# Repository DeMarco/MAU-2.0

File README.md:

View this project on [CADLAB.io](https://cadlab.io/project/1286). 

# MAU-2.0
The expanded version of MAU

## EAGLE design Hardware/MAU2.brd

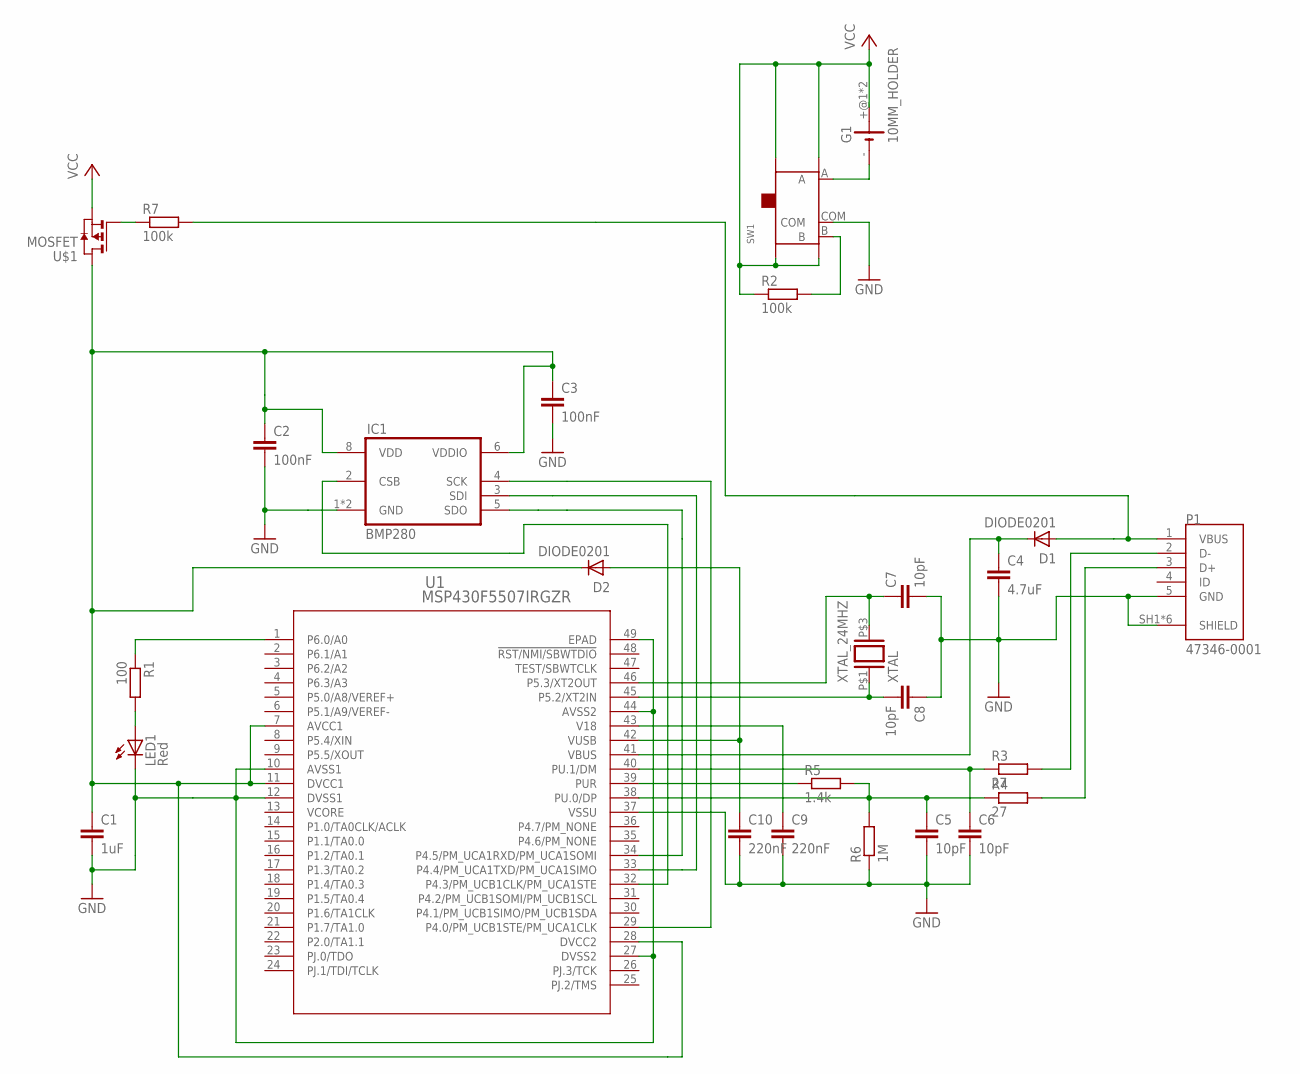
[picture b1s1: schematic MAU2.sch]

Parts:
C1: 1uF; C0201
C2, C3: 100nF; C0201
C4: 4.7uF; C0201
C5, C6, C7, C8: 10pF; C0201
C9, C10: 220nF; C0201
D1, D2: DIODE0201; 0201
G1: 10MM_HOLDER
IC1: BMP280
LED1: Red; CHIPLED_0603
P1: 47346-0001; MOLEX_47346-0001
R1: 100; R0201
R2, R7: 100k; R0201
R3, R4: 27; R0201
R5: 1.4k; R0201
R6: 1M; R0201
SW1: SMD-TOGGLE-SWITCH-ON-ON(3+4P-6.7X2.7MM)SLIDE_LATE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; SW7-SMD-6.7X2.6X1.4MM-90D
U1: MSP430F5507IRGZR; RGZ48_5P15X5P15
U$1: MOSFET; VLM0806
XTAL_24MHZ: XTAL; XTAL_SMD_1612

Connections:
GND: C1.2, C2.2, C3.2, C4.2, C5.2, C6.2, C7.2, C8.1, C9.2, C10.2, IC1.1 (GND), IC1.7 (GND), LED1.C, P1.5 (GND), P1.SH1 (SHIELD), P1.SH2 (SHIELD), P1.SH3 (SHIELD), P1.SH4 (SHIELD), P1.SH5 (SHIELD), P1.SH6 (SHIELD), R6.1, SW1.COM, U1.10 (AVSS1), U1.12 (DVSS1), U1.27 (DVSS2), U1.37 (VSSU), U1.44 (AVSS2), U1.49 (EPAD)
unnamed: G1.-, SW1.A
unnamed: C4.1, D1.1 (C), U1.41 (VBUS)
unnamed: LED1.A, R1.2
unnamed: C6.1, R3.1, U1.40 (PU.1/DM)
unnamed: R2.2, SW1.B
unnamed: C5.1, R4.1, R5.2, R6.2, U1.38 (PU.0/DP)
unnamed: P1.2 (D-), R3.2
unnamed: P1.3 (D+), R4.2
unnamed: R5.1, U1.39 (PUR)
unnamed: C8.2, U1.45 (P5.2/XT2IN), XTAL_24MHZ.P$1 (1)
unnamed: C7.1, U1.46 (P5.3/XT2OUT), XTAL_24MHZ.P$3 (2)
unnamed: C9.1, U1.43 (V18)
unnamed: C10.1, D2.2 (A), U1.42 (VUSB)
unnamed: R7.1, U$1.P$1 (G)
unnamed: IC1.5 (SDO), U1.34 (P4.5/PM_UCA1RXD/PM_UCA1SOMI)
unnamed: IC1.3 (SDI), U1.33 (P4.4/PM_UCA1TXD/PM_UCA1SIMO)
unnamed: IC1.4 (SCK), U1.29 (P4.0/PM_UCB1STE/PM_UCA1CLK)
unnamed: IC1.2 (CSB), U1.32 (P4.3/PM_UCB1CLK/PM_UCA1STE)
unnamed: R1.1, U1.1 (P6.0/A0)
unnamed: D1.2 (A), P1.1 (VBUS), R7.2
VCC: G1.+@1 (+), G1.+@2 (+), R2.1, SW1.P1 (SS4), SW1.P2 (SS3), SW1.P3 (SS2), SW1.P4 (SS1), U$1.P$2 (S)
VCC-FET: C1.1, C2.1, C3.1, D2.1 (C), IC1.6 (VDDIO), IC1.8 (VDD), U1.7 (AVCC1), U1.11 (DVCC1), U1.28 (DVCC2), U$1.P$3 (D)
VCORE: U1.13 (VCORE)

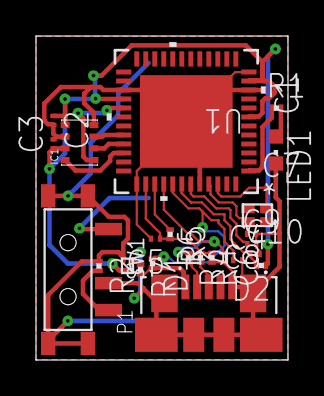
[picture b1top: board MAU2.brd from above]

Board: 2 copper layers, 14.0 x 18.0 mm, 27 parts (0 on the bottom side), 23 nets.

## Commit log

2018-07-29 Updating gitignore
2018-09-09 Adding EAGLE to gitignore file
2018-09-09 Brought HW project to main repository
2018-09-09 Backlink to CADLAB.io has been added.
2018-10-06 MSP430 basic and USB connections (work in progress)
2018-10-07 Schematics complete
    Added connections between MOSFET and DVcc;
    Added SPI connections between MSP430 and BMP280;
    Added connection between LED and MSP430.
2018-10-07 All CPU needed pins connected and CPU positioned in the board
2018-10-07 All components positioned
2018-10-07 Ratsnet Polygon updated to cover the whole board
2018-10-07 Routing in progress, set BMP280 supply to VCC-FET
2018-10-07 Finished routing
    DVCC2 and RST capacitors removed.
2019-07-12 Adding GNU GPL-v3.0 license
